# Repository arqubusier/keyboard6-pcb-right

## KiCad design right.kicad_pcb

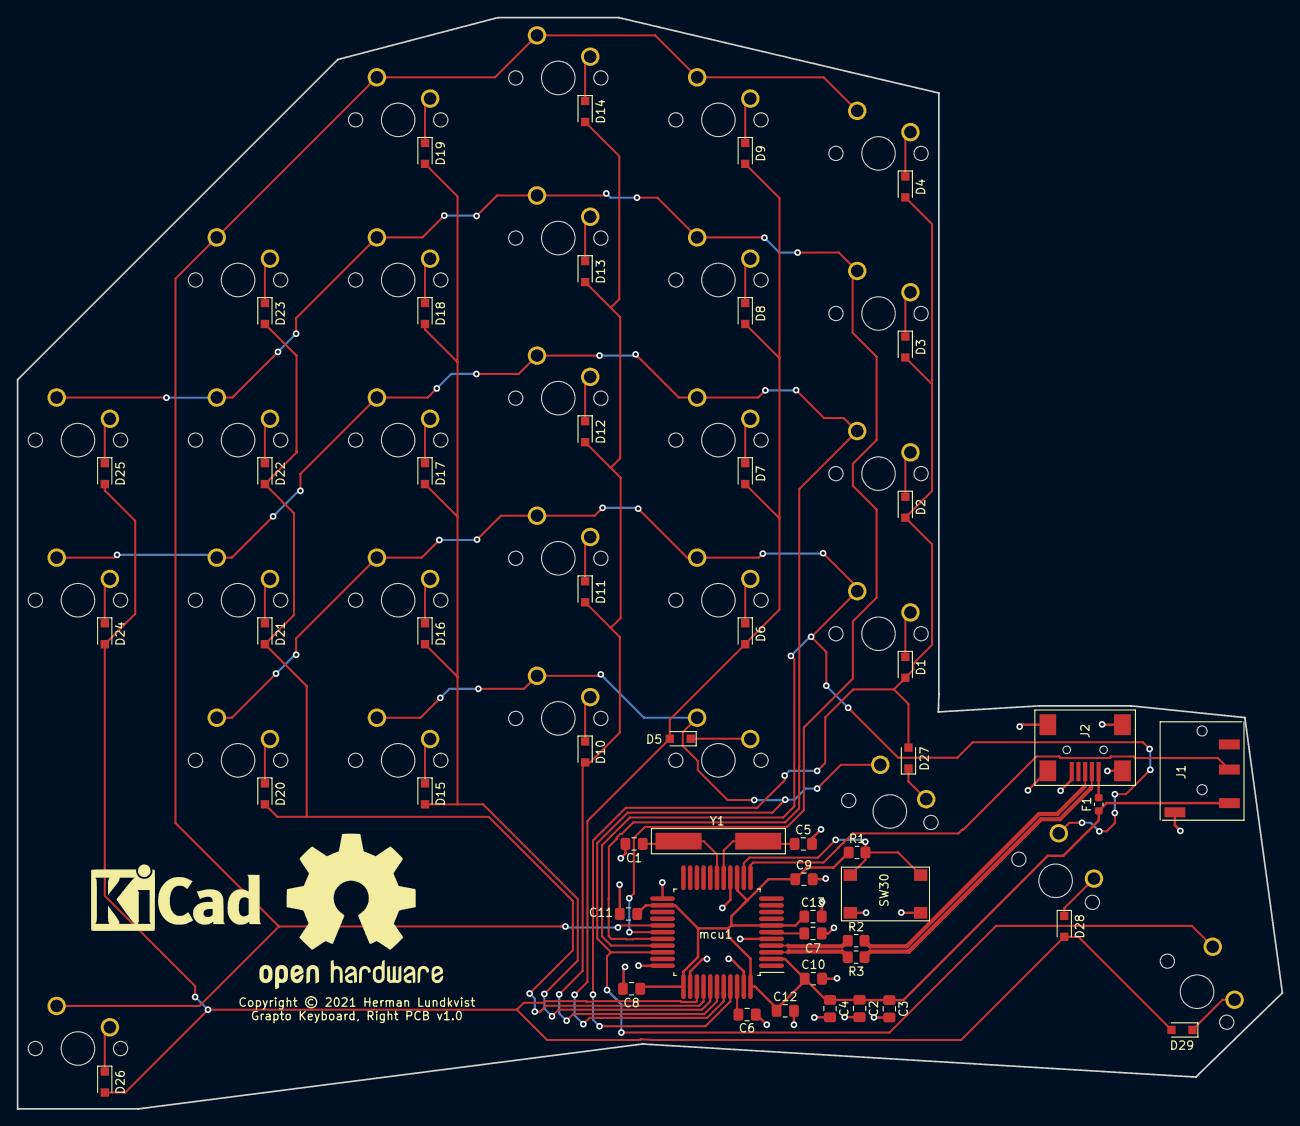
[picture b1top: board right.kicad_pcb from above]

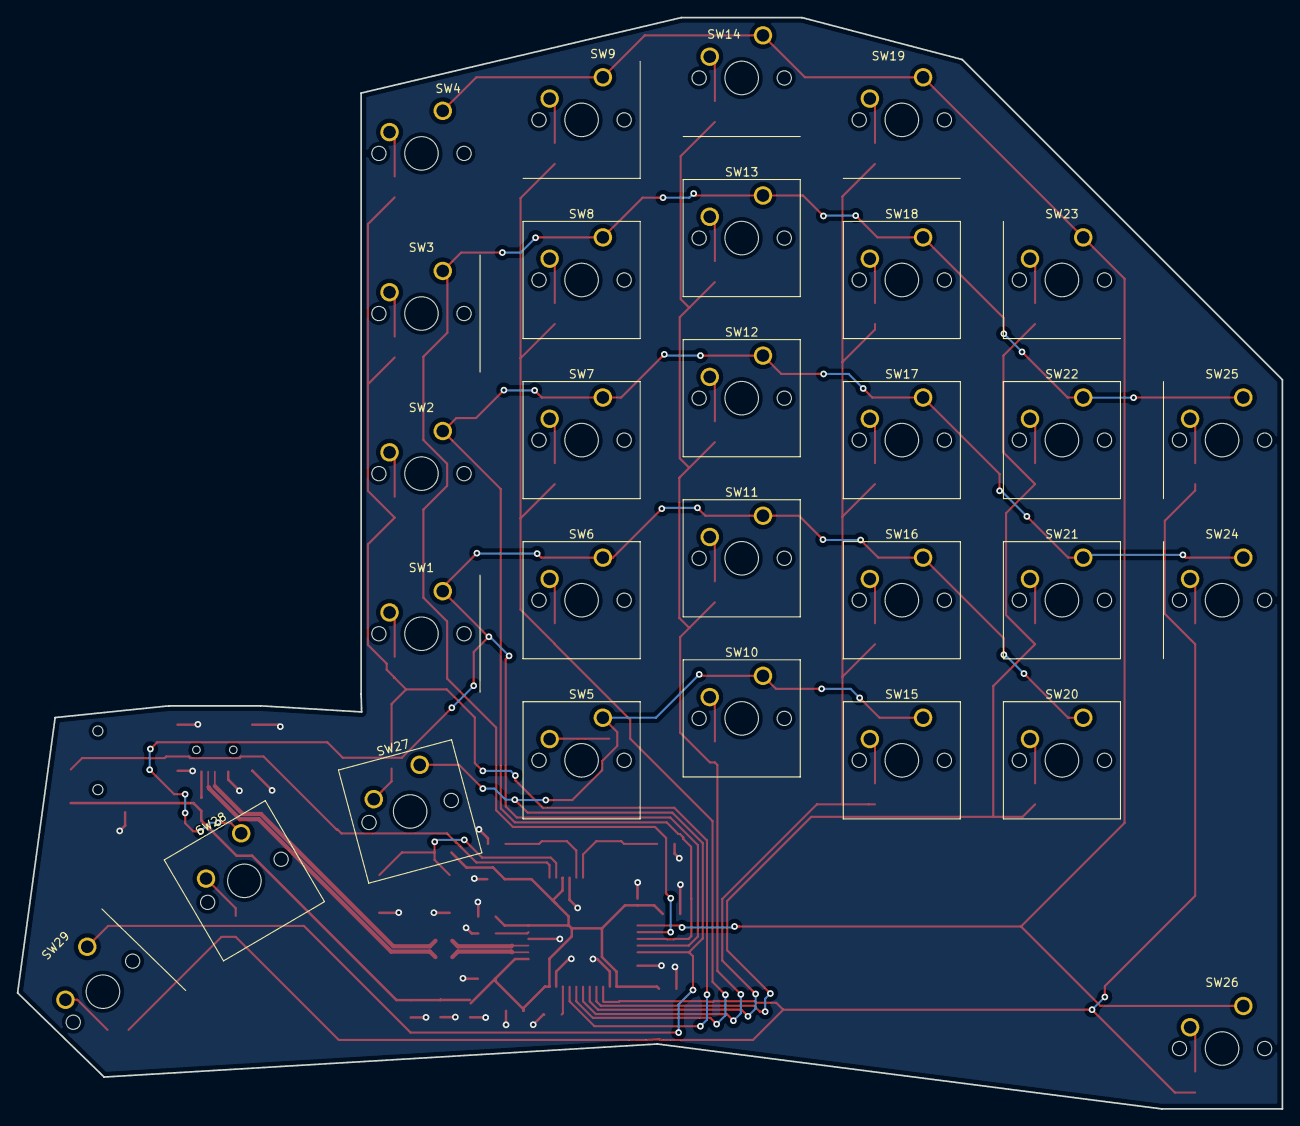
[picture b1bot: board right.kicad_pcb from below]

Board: 2 copper layers, 150.9 x 130.2 mm, 80 parts (29 on the bottom side), 53 nets.

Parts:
C1, C5: 32p; C_0805_2012Metric_Pad1.18x1.45mm_HandSolder
C2, C7: 1u; C_0805_2012Metric_Pad1.18x1.45mm_HandSolder
C3, C6, C8, C9, C10, C11, C12, C13: 0.1u; C_0805_2012Metric_Pad1.18x1.45mm_HandSolder
C4: 10u; C_0805_2012Metric_Pad1.18x1.45mm_HandSolder
D1, D2, D3, D4, D5, D6, D7, D8, D9, D10, D11, D12, D13, D14, D15, D16, D17, D18, D19, D20, D21, D22, D23, D24, D25, D26, D27, D28, D29: DIODE; D_SOD-323_HandSoldering
F1: 500m; Fuse_0603_1608Metric
J1: AudioJack4; TRRS_smd_SparkFun_PRT-12639
J2: USB_B_Micro; USB_mini_b_TE_ 1734035-2
R1: 4.7k; R_0805_2012Metric_Pad1.20x1.40mm_HandSolder
R2, R3: 22; R_0805_2012Metric_Pad1.20x1.40mm_HandSolder
SW1, SW2, SW3, SW4, SW5, SW6, SW7, SW8, SW9, SW10, SW11, SW12, SW13, SW14, SW15, SW16, SW17, SW18, SW19, SW20, SW21, SW22, SW23, SW24, SW25, SW26, SW27, SW28, SW29: SW_DIP_x01; SW_Cherry_MX_1.00u_PCB_centered
SW30: SW_Push_Dual; SW_E_SW_TL_3303
Y1: 16MHz; Crystal_CSM-7X_SMD
mcu1: ATmega32U4-AU; QFP-44_10x10_Pitch0.8mm_Hand_solder

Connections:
/Sheet60738A9D/col0: D24.2, D25.2, D26.2, D28.2, D29.2, mcu1.36
/Sheet60738A9D/col1: D20.2, D21.2, D22.2, D23.2, mcu1.37
/Sheet60738A9D/col2: D15.2, D16.2, D17.2, D18.2, D19.2, mcu1.38
/Sheet60738A9D/col3: D10.2, D11.2, D12.2, D13.2, D14.2, mcu1.39
/Sheet60738A9D/col4: D5.2, D6.2, D7.2, D8.2, D9.2, mcu1.40
/Sheet60738A9D/col5: D1.2, D2.2, D3.2, D4.2, D27.2, mcu1.41
/Sheet60738A9D/row0: SW4.1, SW9.1, SW14.1, SW19.1, SW23.1, SW26.1, mcu1.27
/Sheet60738A9D/row1: SW3.1, SW8.1, SW13.1, SW18.1, SW22.1, SW25.1, mcu1.28
/Sheet60738A9D/row2: SW2.1, SW7.1, SW12.1, SW17.1, SW21.1, SW24.1, mcu1.29
/Sheet60738A9D/row3: SW1.1, SW6.1, SW11.1, SW16.1, SW20.1, SW28.1, mcu1.30
/Sheet60738A9D/row4: SW5.1, SW10.1, SW15.1, SW27.1, SW29.1, mcu1.31
/Sheet60738E4E/USB_FULL1_N: J2.2, R3.2
/Sheet60738E4E/USB_FULL1_P: J2.3, R2.2
/Sheet60738E4E/USB_FULL_N: R3.1, mcu1.3
/Sheet60738E4E/USB_FULL_P: R2.1, mcu1.4
/Sheet60738E4E/VBUS: F1.2, J2.1
GND1: C1.2, C2.2, C3.2, C4.2, C5.2, C6.2, C7.2, C8.2, C9.2, C10.2, C11.2, C12.2, C13.2, J1.S, J2.5, J2.6, SW30.1, SW30.3, mcu1.5, mcu1.15, mcu1.23, mcu1.33, mcu1.35, mcu1.43
unnamed: C1.1, Y1.1, mcu1.17
unnamed: C5.1, Y1.2, mcu1.16
unnamed: C6.1, mcu1.42
unnamed: C7.1, mcu1.6
unnamed: D1.1, SW1.2
unnamed: D2.1, SW2.2
unnamed: D3.1, SW3.2
unnamed: D4.1, SW4.2
unnamed: D5.1, SW5.2
unnamed: D6.1, SW6.2
unnamed: D7.1, SW7.2
unnamed: D8.1, SW8.2
unnamed: D9.1, SW9.2
unnamed: D10.1, SW10.2
unnamed: D11.1, SW11.2
unnamed: D12.1, SW12.2
unnamed: D13.1, SW13.2
unnamed: D14.1, SW14.2
unnamed: D15.1, SW15.2
unnamed: D16.1, SW16.2
unnamed: D17.1, SW17.2
unnamed: D18.1, SW18.2
unnamed: D19.1, SW19.2
unnamed: D20.1, SW20.2
unnamed: D21.1, SW21.2
unnamed: D22.1, SW22.2
unnamed: D23.1, SW23.2
unnamed: D24.1, SW24.2
unnamed: D25.1, SW25.2
unnamed: D26.1, SW26.2
unnamed: D27.1, SW27.2
unnamed: D28.1, SW28.2
unnamed: D29.1, SW29.2
unnamed: J1.R1, mcu1.12
unnamed: R1.2, SW30.2, SW30.4, mcu1.13
UVCC: C2.1, C3.1, C4.1, C8.1, C9.1, C10.1, C11.1, C12.1, C13.1, F1.1, J1.T, R1.1, mcu1.2, mcu1.7, mcu1.14, mcu1.24, mcu1.34, mcu1.44

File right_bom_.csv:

Component,Description,Part,References,Value,Footprint,Quantity Per PCB,Datasheet,Manufacturer Part Number,Mouser Part Number
1,Unpolarized capacitor,C,C1 C5,32p,C_0805_2012Metric_Pad1.18x1.45mm_HandSolder,2,~,GQM2195C2E320JB12D,81-GQM2195C2E320JB2D
2,Unpolarized capacitor,C,C3 C6 C8 C9 C10 C11 C12 C13,0.1u,C_0805_2012Metric_Pad1.18x1.45mm_HandSolder,8,~,08053C104KAT2A,581-08053C104K
3,Unpolarized capacitor,C,C2 C7,1u,C_0805_2012Metric_Pad1.18x1.45mm_HandSolder,2,~,CL21B105KOFNNNE,187-CL21B105KOFNNNE
4,Unpolarized capacitor,C,C4,10u,C_0805_2012Metric_Pad1.18x1.45mm_HandSolder,1,~,JMF212AB7106KGHT,963-JMF212AB7106KGHT
5,Diode,D,D1 D2 D3 D4 D5 D6 D7 D8 D9 D10 D11 D12 D13 D14 D15 D16 D17 D18 D19 D20 D21 D22 D23 D24 D25 D26 D27 D28 D29,DIODE,D_SOD-323_HandSoldering,29,~,1N4148WX-TP,833-1N4148WX-TP
6,Fuse,Fuse,F1,500m,Fuse_0603_1608Metric,1,~,TR-0603HV500-R,504-TR-0603HV500-R
7,"Audio Jack, 4 Poles (TRRS)",AudioJack4,J1,AudioJack4,TRRS_smd_SparkFun_PRT-12639,1,~,PRT-12639,474-PRT-12639
8,USB Micro Type B connector,USB_B_Micro,J2,USB_B_Micro,USB_mini_b_TE_ 1734035-2,1,~,1734035-2,571-1734035-2
9,Resistor,R,R2 R3,22,R_0805_2012Metric_Pad1.20x1.40mm_HandSolder,2,~,CR0805-FX-22R0ELF,652-CR0805FX-22R0ELF
10,Resistor,R,R1,4.7k,R_0805_2012Metric_Pad1.20x1.40mm_HandSolder,1,~,CRCW08054K70JNEA,71-CRCW0805J-4.7K-E3
11,"1x DIP Switch, Single Pole Single Throw (SPST) switch, small symbol",SW_DIP_x01,SW1 SW2 SW3 SW4 SW5 SW6 SW7 SW8 SW9 SW10 SW11 SW12 SW13 SW14 SW15 SW16 SW17 SW18 SW19 SW20 SW21 SW22 SW23 SW24 SW25 SW26 SW27 SW28 SW29,SW_DIP_x01,SW_Cherry_MX_1.00u_PCB_centered,29,~,MX1A-G1NN,540-MX1A-G1NN
12,"Push button switch, generic, symbol, four pins",SW_Push_Dual,SW30,SW_Push_Dual,SW_E_SW_TL_3303,1,~,TL3303F160QG,612-TL3303F160QG
13,"Two pin crystal, small symbol",Crystal_Small,Y1,16MHz,Crystal_CSM-7X_SMD,1,~,ECS-160-20-5PX-TR,520-CSM1600-20-X
14,"16MHz, 32kB Flash, 2.5kB SRAM, 1kB EEPROM, USB 2.0, TQFP-44",ATmega32U4-AU,mcu1,ATmega32U4-AU,QFP-44_10x10_Pitch0.8mm_Hand_solder,1,http://ww1.microchip.com/downloads/en/DeviceDoc/Atmel-7766-8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,,





Component Groups:,14
Component Count:,80
Fitted Components:,80
Number of PCBs:,1
Total components:,80
Schematic Version:,
Schematic Date:,
PCB Variant:,default
BoM Date:,Sun 25 Apr 2021 12:26:25 PM CEST
Schematic Source:,right.sch
KiCad Version:,Eeschema 5.1.9

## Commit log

2021-04-05 Fixed annotations.
2021-04-18 Update common.
2021-04-18 Initial positions set.
2021-04-18 Components placed.
2021-04-24 Layout done.
2021-04-24 added bom
2021-04-25 Minor changes
2021-04-25 Fix silkscreen clearance.

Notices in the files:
right.kicad_pcb:
Copyright © 2021 Herman Lundkvist
